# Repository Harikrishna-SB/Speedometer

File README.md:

# Speedometer
just for toy cars :)

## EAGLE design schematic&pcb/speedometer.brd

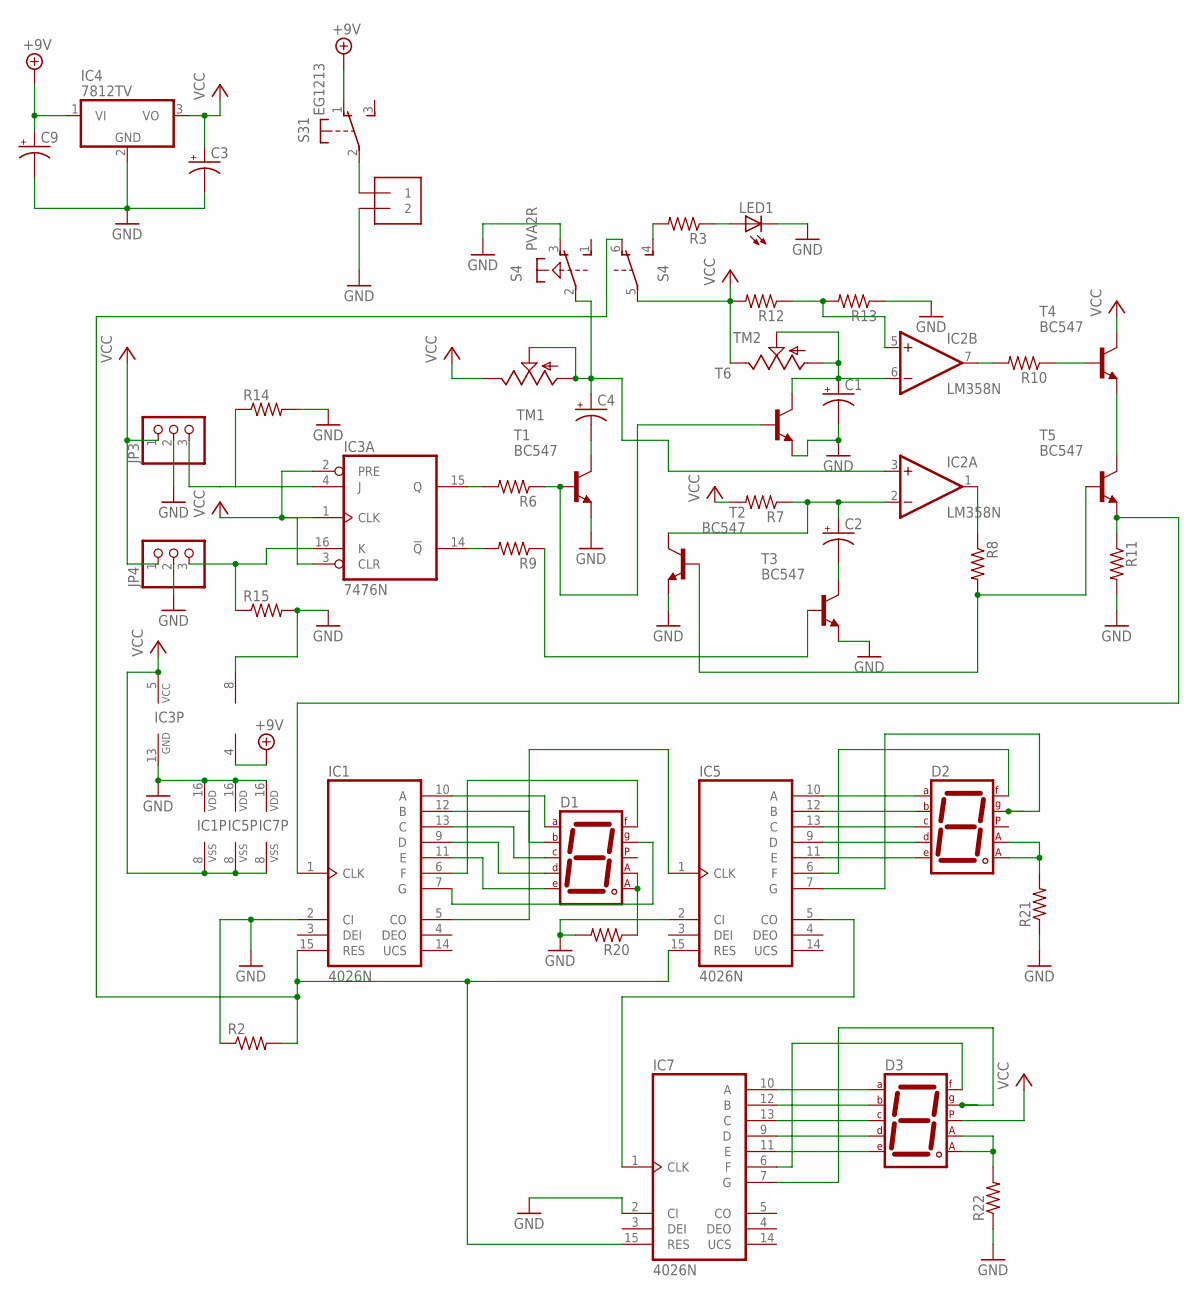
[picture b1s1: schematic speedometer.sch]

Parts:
C1, C2, C3, C4: CPOL-USE2-4; E2-4
C9: CPOL-USE2.5-6; E2,5-6
D1, D2, D3: 7SEG-CA; 7SEG-13
IC1, IC5, IC7: 4026N; DIL16
IC2: LM358N; DIL08
IC3: 7476N; DIL16
IC4: 7812TV; TO220V
J1: 1X2-3.5MM
JP3, JP4: PINHD-1X3; 1X03
LED1: LED5MM
R2, R3, R6, R7, R8, R9, R10, R11, R12, R13, R14, R15, R20, R21, R22: R-US_0204/7; 0204/7
S3: EG1213
S4: PVA2R
T1, T2, T3, T4, T5, T6: BC547; TO92
TM1, TM2: TRIM; 6MM

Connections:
+9V: C9.+, IC2.4 (V-), IC4.1 (VI), S3.1 (O)
GND: C1.-, C3.-, C9.-, IC1.2 (CI), IC1.16 (VDD), IC2.8 (V+), IC3.13 (GND), IC4.2 (GND), IC5.2 (CI), IC5.16 (VDD), IC7.2 (CI), IC7.16 (VDD), J1.2, JP3.2, JP4.2, LED1.K (C), R2.1, R11.2, R13.1, R14.2, R15.2, R20.2, R21.1, R22.1, S4.3 (O), T1.1 (E), T2.1 (E), T3.1 (E), T6.1 (E)
unnamed: IC3.4 (J), JP3.3, R14.1
unnamed: IC3.16 (K), JP4.3, R15.1
unnamed: R3.2, S4.4 (S)
unnamed: C4.-, T1.3 (C)
unnamed: C4.+, IC2.3 (+IN), S4.2, TM1.A, TM1.S
unnamed: R6.1, T1.2 (B), T6.2 (B)
unnamed: IC1.15 (RES), IC5.15 (RES), IC7.15 (RES), R2.2, S4.6 (O)
unnamed: IC3.15 (Q), R6.2
unnamed: C2.+, IC2.2 (-IN), R7.1, T2.3 (C)
unnamed: R8.2, T2.2 (B), T5.2 (B)
unnamed: IC3.14 (!Q), R9.2
unnamed: IC2.1 (OUT), R8.1
unnamed: LED1.A, R3.1
unnamed: R9.1, T3.2 (B)
unnamed: C2.-, T3.3 (C)
unnamed: IC2.7 (OUT), R10.2
unnamed: R10.1, T4.2 (B)
unnamed: T4.1 (E), T5.3 (C)
unnamed: IC2.5 (+IN), R12.1, R13.2
unnamed: C1.+, IC2.6 (-IN), T6.3 (C), TM2.A, TM2.S
unnamed: D1.7 (A), IC1.10 (A)
unnamed: D1.3 (CA1), D1.8 (CA2), R20.1
unnamed: D1.6 (B), IC1.12 (B)
unnamed: IC1.1 (CLK), R11.1, T5.1 (E)
unnamed: D1.2 (D), IC1.9 (D)
unnamed: D1.4 (C), IC1.13 (C)
unnamed: D1.1 (E), IC1.11 (E)
unnamed: D1.9 (F), IC1.6 (F)
unnamed: D1.10 (G), IC1.7 (G)
unnamed: IC1.5 (CO), IC5.1 (CLK)
unnamed: D2.3 (CA1), D2.8 (CA2), R21.2
unnamed: D2.7 (A), IC5.10 (A)
unnamed: D2.6 (B), IC5.12 (B)
unnamed: D2.4 (C), IC5.13 (C)
unnamed: D2.2 (D), IC5.9 (D)
unnamed: D2.1 (E), IC5.11 (E)
unnamed: D2.9 (F), IC5.6 (F)
unnamed: D2.10 (G), IC5.7 (G)
unnamed: IC5.5 (CO), IC7.1 (CLK)
unnamed: J1.1, S3.2
unnamed: D3.7 (A), IC7.10 (A)
unnamed: D3.6 (B), IC7.12 (B)
unnamed: D3.4 (C), IC7.13 (C)
unnamed: D3.2 (D), IC7.9 (D)
unnamed: D3.1 (E), IC7.11 (E)
unnamed: D3.9 (F), IC7.6 (F)
unnamed: D3.10 (G), IC7.7 (G)
unnamed: D3.3 (CA1), D3.8 (CA2), R22.2
VCC: C3.+, D3.5 (DP), IC1.8 (VSS), IC3.1 (CLK), IC3.2 (PRE), IC3.3 (CLR), IC3.5 (VCC), IC4.3 (VO), IC5.8 (VSS), IC7.8 (VSS), JP3.1, JP4.1, R7.2, R12.2, S4.5, T4.3 (C), TM1.E, TM2.E

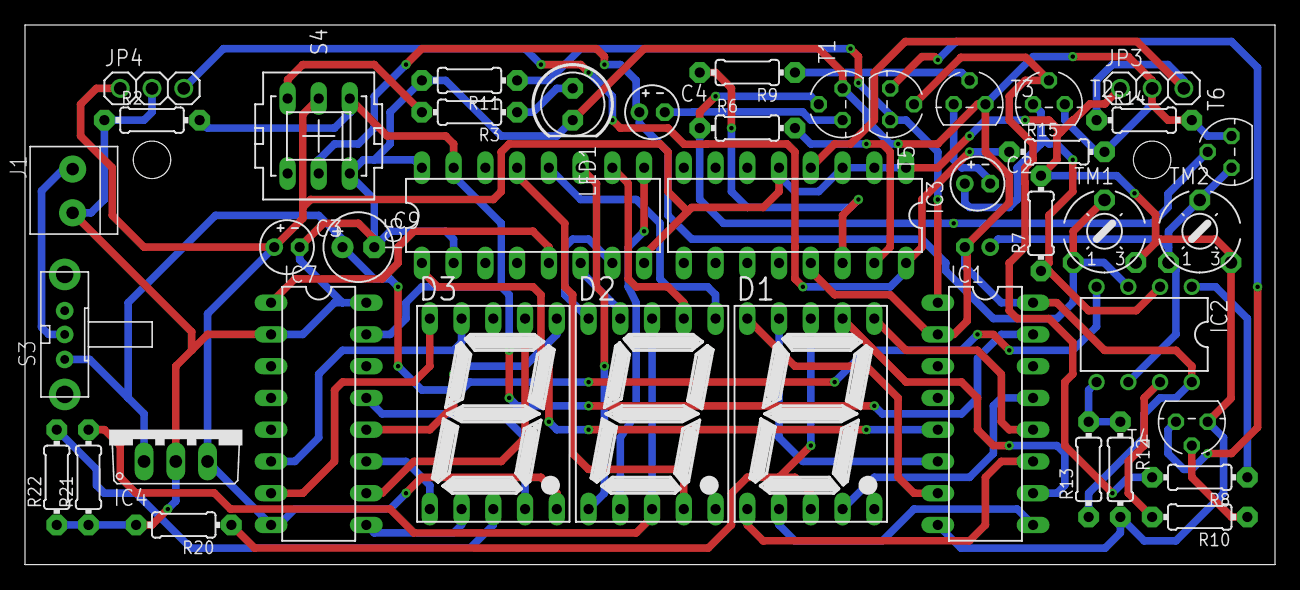
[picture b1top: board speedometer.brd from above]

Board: 2 copper layers, 100.0 x 43.2 mm, 43 parts (1 on the bottom side), 51 nets.

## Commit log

2020-04-02 schematic and layout added
